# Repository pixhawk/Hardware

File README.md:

# Pixhawk Hardware Designs

<div align="center">

</div>

[Pixhawk](http://pixhawk.org) is an independent open-hardware project that aims to provide "the gold standard" for readily-available, hiqh-quality and low-cost autopilot hardware designs for the academic, hobby and developer communities.
Pixhawk supports multiple flight stacks: PX4 ® and ArduPilot ®.

> [!NOTE]
> Designs are provided for a number of components used in unmanned vehicles, including: Autopilots (Flight Management Units - FMUs), ESCs (electronic speed controllers), optical flow sensors, etc.

## What are Open Hardware Designs?

The [Pixhawk project](https://pixhawk.org/) provides open hardware designs following the [OSHW 1.1 definition](https://www.oshwa.org/definition/).

In essence, this definition allows anyone to freely study, modify, distribute, make, and sell the designs (or hardware based on the designs) under the terms of a particular [open source licence](#licensing).

## Hardware Designs

Hardware designs delivered by the project are listed below.

<span id="fmu_designs"></span>

### FMU (Autopilot) Designs

Pixhawk FMU open designs include all information required to create an autopilot hardware product that is *firmware compatible* with other hardware created from the same design.
Manufacturers are encouraged to take the designs and create products that are best suited to a particular market or use case (e.g. for very small vehicles, or those that operate at environmental extremes).

> [!NOTE]
> While a physical connector standard is not mandated, newer products generally follow the [Pixhawk Connector Standard](https://pixhawk.org/pixhawk-connector-standard/).

#### Design Specifications

Designs are *usually* specified in the form of *schematics* that show all included components (CPU, sensors, etc.), how they are connected, and their pin mappings.
They may also include a BOM (bill of materials).

> [!NOTE]
> Not all designs deliver schematics.
> A minimal design needs to contain enough information for manufacturers to create a compatible products; this can also be achieved using a precise pinout definition and information about connections of internal/external busses, etc.

#### Open Reference Hardware

The project provides *open reference hardware/layouts* for **some** open designs, in some versions.
These are provided in the form of PCB layout files.

The reference hardware files are shared under the same [license](#licenses) as the associated open design, and hence may be used in the same way(s).

#### FMU Versions

The Pixhawk project has evolved the FMU design through a number of verisons.

These are named using the designation: FMUvX (e.g.: FMUv1, FMUv2, FMUv3, FMUv4, etc.).
Higher FMU numbers indicate that the board is more recent, but may not indicate increased capability (versions can be almost identical - differing only in connector wiring).

The versions are listed below (with a high level overview of the main differences).

Version | Year | Lead Product | CPU | Other
--- | --- | --- | --- | ---
[FMUv1](FMUv1/README.md) & [IOv1](IOv1) | 2012 | None | 168 MHz M4 | (Discontinued) Original Flight Management Unit and Separate I/O board.
[FMUv2](FMUv2/README.md) | 2013 | Pixhawk 1 | 168 MHz M4 | Single board with STM32427VI processor.
[FMUv3](FMUv3_REV_D/README.md) | 2015 | Pixhawk 2 | 168 MHz M4 | Redundant sensors. Identical to FMUv2, but usable flash doubled to 2MB.
[FMUv4](FMUv4/README.md) | 2015 | Pixracer | 168 MHz M4 | Increased RAM. Faster CPU. More serial ports. No IO processor.
FMUv4X | 2017 | Pixhawk 3 Pro | 168 MHz M4 | Slightly increased RAM. More serial ports. IO processor. Redundant sensors.
[FMUv5](FMUv5/README.md) | 2018 | Pixhawk 4 | 200 MHz M7 | New processor (F7). Much faster. More RAM. More CAN busses. Much more configurable.<br>> **Note** Minimum specification provided (pinout info, but no schematics).
FMUv5X | 2019 | Pixhawk 5X | 200 MHz M7 | Temp-calibrated, redundant sensors.

> [!NOTE]
> Products based on Pixhawk designs are listed here: [PX4 User Guide > Pixhawk Series](https://docs.px4.io/main/en/flight_controller/pixhawk_series.html#pixhawk-series).

#### Derived FMU Products

Commercial products that are *derived* (under the terms of the open source license) from the Pixhawk FMU designs must provide their schematics and other information.

Relevant products are listed below:

- [MindPX V2 Hardware](MindPXv2/README.md)

### Sapog ESC

- [Sapog ESC](https://github.com/PX4/sapog) Hardware - The directory [sapog_reference_hardware](sapog_reference_hardware/README.md) contains the reference hardware design for the Sapog ESC firmware.

### Other

- [AIRSPEEDv1](AIRSPEEDv1) - 
- [FLOWv1](FLOWv1)
- [IMUv3_REV_C](IMUv3_REV_C)
- [PSMv3_REV_C](PSMv3_REV_C)

## Dev Call

Pixhawk standards are developed in a weekly public developer call.

The call is shown in the [Dronecode calendar](https://www.dronecode.org/calendar/) as: *Pixhawk Hardware Standards Weekly Call* (all call details are in the entry).

<span id="licensing"></span>
## Licensing and Trademarks

Pixhawk project schematics and reference designs are licensed under [CC BY-SA 3](https://creativecommons.org/licenses/by-sa/3.0/legalcode).

The license allows you to use, sell, share, modify and build on the files in almost any way you like - provided that you give credit/attribution, and that you share any changes that you make under the same open source license (see the [human readable version of the license](https://creativecommons.org/licenses/by-sa/3.0/) for a concise summary of the rights and obligations).

> [!NOTE]
> Boards that are *derived directly* from Pixhawk schematic files (or reference boards) must be open sourced.
> They can't be commercially licensed as proprietary products.

Manufacturers can create (compatible) *fully independent products* by first generating fresh schematic files that have the same pin mapping/components as the FMU designs.
Products that are based on independently created schematics are considered original works, and can be licensed as required.

## Trademarks

The term *Pixhawk* is a trademark, and may not be used in product names without explicit permission from the trademark owner.

Typically this trademark is granted to the first board based on a particular FMU design and/or boards that use Pixhawk open reference hardware layouts.

> [!NOTE]
> A "Pixhawk" is an autopilot that has been been given permission to use the Pixhawk trademark in its name.
> While other boards are based on the "Pixhawk FMU Standard", the are not *strictly speaking* "Pixhawks".

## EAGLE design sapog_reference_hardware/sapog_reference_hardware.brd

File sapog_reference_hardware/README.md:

# Reference Hardware for PX4 Sapog

This directory contains the reference hardware design for
[PX4 Sapog](https://kb.zubax.com/x/cYAh) - an advanced open source ESC firmware.

This specific design is intended as an application note;
the main knowledge to gather from this design is the pinout of the MCU and its immediate connections.
The design is implemented in Eagle, version 7 or newer is required.

## Resources

* **[HOMEPAGE](https://kb.zubax.com/x/cYAh)**
* **[SUPPORT & FEEDBACK](https://forum.zubax.com/)**
* **[FIRMWARE ON GITHUB](https://github.com/PX4/sapog)**

## Design guidelines

1. When choosing the power transistors, keep their dynamic characteristics in mind:
the switching time must be under 50 nanoseconds.
Sapog employs somewhat unorthodox methods of state estimation which require a high-speed inverter.
2. The RC filters in the phase voltage feedback circuits should be designed so that their cutoff frequency
is around 19 kHz and the output impedance does not exceed 8 kohm.
3. Unless your maximum supply voltage exceeds 25 V (6S), do not change the DC link voltage measurement divider.

## License

The design is distributed under the terms of the
Creative Commons Attribution-ShareAlike 3.0 Unported license (CC BY-SA 3.0).

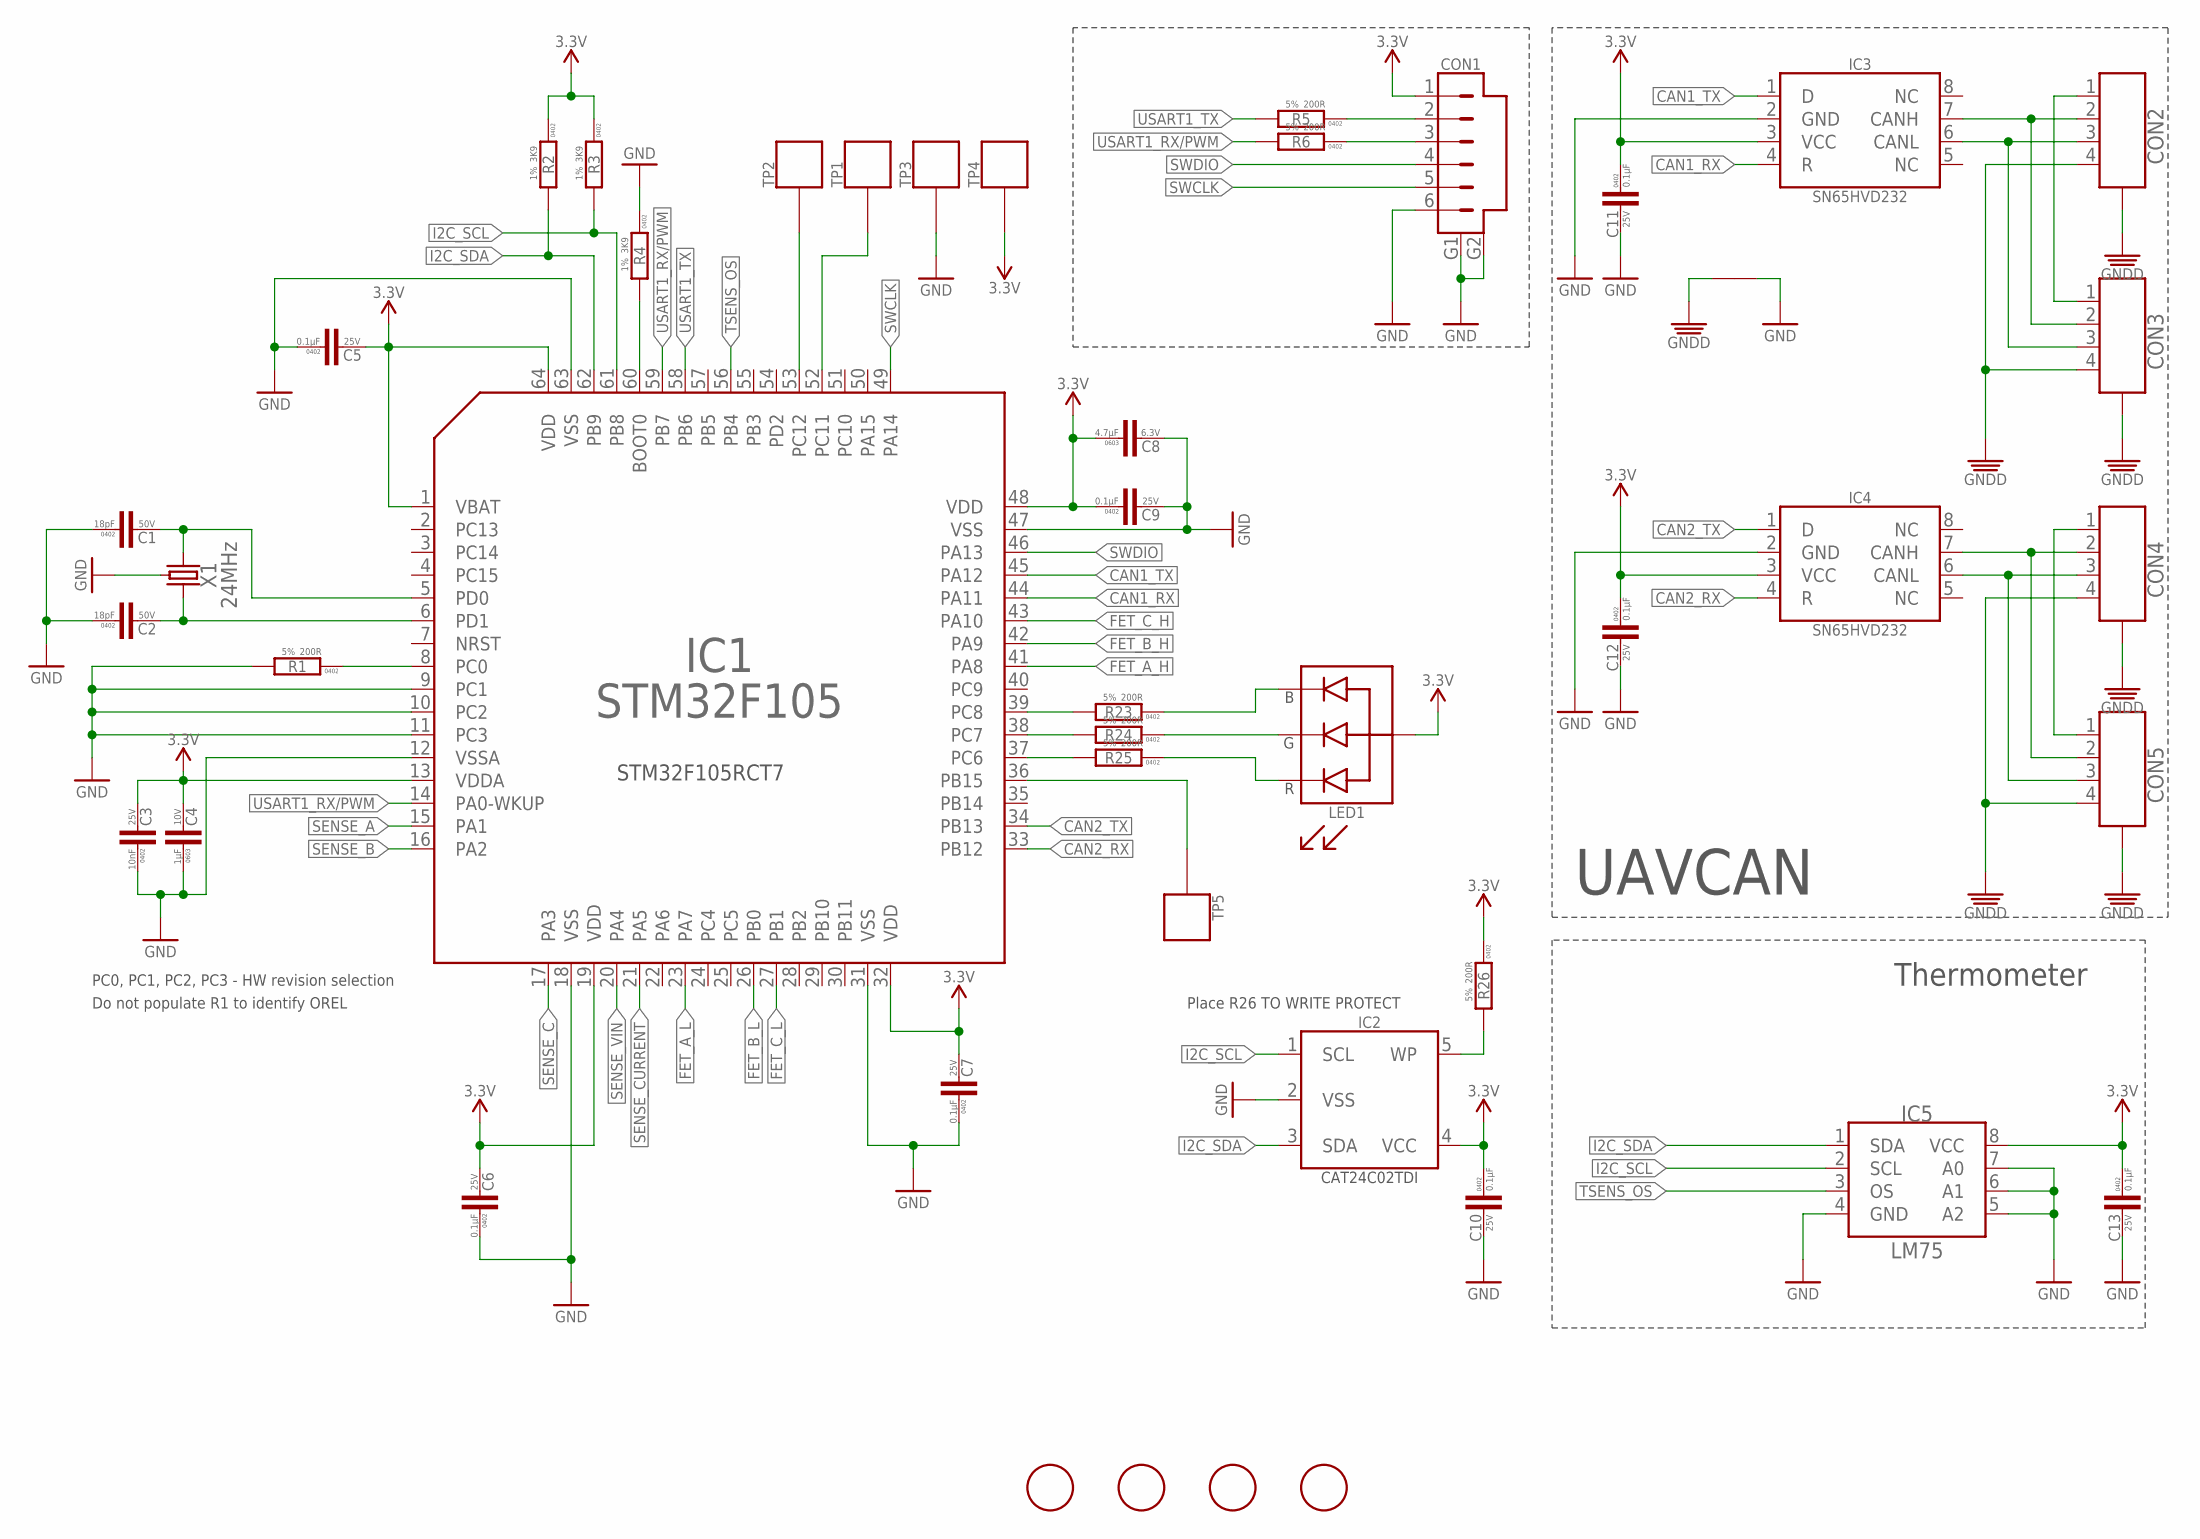
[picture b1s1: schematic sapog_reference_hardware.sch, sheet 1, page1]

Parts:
C1, C2: 18pF; C0402
C3: 10nF; C0402
C4: 1µF; C0603
C5, C6, C7, C9, C10, C11, C12, C13: 0.1µF; C0402
C8: 4.7µF; C0603
CON1: SM06B-SRSS-TB; SM06B; PARTNO SM06B-SRSS-TB
CON2, CON3, CON4, CON5: CON-4P-RA-JST_GH; JST_GH-4P-RA
FD1, FD2, FD3, FD4: FIDUCIALMOUNT; FIDUCIA-MOUNT
IC1: STM32F105; TQFP64-10X10; DIGIKEY# 497-11547-ND
IC2: CAT24C02; SOT23-5L
IC3, IC4: SN65HVD232D; SOIC8
IC5: LM75BD-TSSOP8; TSSOP8
LED1: LTST-C19HE1WT; LITE_ON_RGB_LED
R1: 200R; R0402
R2, R3, R4: 3K9; R0402
R5, R6, R23, R24, R25, R26: 200R; R0402; PARTNO RC0402FR-07240RL
TP1, TP2, TP3, TP4, TP5: PAD.05; PAD.05X.05; PARTNO *
U$2: CONNECTION
X1: 24MHz; OSCILLATOR-3.2X2.5; DIGIKEY# 1253-1198-1-ND

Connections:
BOOT0: IC1.60 (BOOT0), R4.2
CAN1_RX: IC1.44 (PA11), IC3.4 (R)
CAN1_TX: IC1.45 (PA12), IC3.1 (D)
CAN2_RX: IC1.33 (PB12), IC4.4 (R)
CAN2_TX: IC1.34 (PB13), IC4.1 (D)
FET_A_H: IC1.41 (PA8); also elsewhere on the board
FET_A_L: IC1.23 (PA7); also elsewhere on the board
FET_B_H: IC1.42 (PA9); also elsewhere on the board
FET_B_L: IC1.26 (PB0); also elsewhere on the board
FET_C_H: IC1.43 (PA10); also elsewhere on the board
FET_C_L: IC1.27 (PB1); also elsewhere on the board
GND: C1.1, C2.1, C3.1, C4.P$1 (1), C5.1, C6.1, C7.1, C8.P$2 (2), C9.2, C10.2, C11.2, C12.2, C13.2, CON1.6, CON1.G1, CON1.G2, IC1.9 (PC1), IC1.10 (PC2), IC1.11 (PC3), IC1.12 (VSSA), IC1.18 (VSS), IC1.31 (VSS), IC1.47 (VSS), IC1.63 (VSS), IC2.2 (VSS), IC3.2 (GND), IC4.2 (GND), IC5.4 (GND), IC5.5 (A2), IC5.6 (A1), IC5.7 (A0), R1.2, R4.1, TP3.P$1, U$2.P$2, X1.2 (GND), X1.4 (GND); also elsewhere on the board
GNDD: CON2.4, CON2.M$0 (GND), CON2.M$1 (GND), CON3.4, CON3.M$0 (GND), CON3.M$1 (GND), CON4.4, CON4.M$0 (GND), CON4.M$1 (GND), CON5.4, CON5.M$0 (GND), CON5.M$1 (GND), U$2.P$1
I2C_SCL: IC1.61 (PB8), IC2.1 (SCL), IC5.2 (SCL), R3.2
I2C_SDA: IC1.62 (PB9), IC2.3 (SDA), IC5.1 (SDA), R2.2
unnamed: CON1.2, R5.1
unnamed: CON1.3, R6.1
unnamed: IC1.37 (PC6), R25.2
unnamed: LED1.B, R23.1
unnamed: LED1.R, R25.1
unnamed: IC1.8 (PC0), R1.1
unnamed: IC2.5 (WP), R26.2
unnamed: IC1.38 (PC7), R24.2
unnamed: C1.2, IC1.5 (PD0), X1.3 (2)
unnamed: IC1.39 (PC8), R23.2
unnamed: CON4.1, CON5.1
unnamed: CON4.2, CON5.2, IC4.7 (CANH)
unnamed: C2.2, IC1.6 (PD1), X1.1
unnamed: CON2.1, CON3.1
unnamed: CON2.2, CON3.2, IC3.7 (CANH)
unnamed: CON4.3, CON5.3, IC4.6 (CANL)
unnamed: CON2.3, CON3.3, IC3.6 (CANL)
unnamed: LED1.G, R24.1
unnamed: IC1.53 (PC12), TP2.P$1
unnamed: IC1.36 (PB15), TP5.P$1
unnamed: IC1.52 (PC11), TP1.P$1
SENSE_A: IC1.15 (PA1); also elsewhere on the board
SENSE_B: IC1.16 (PA2); also elsewhere on the board
SENSE_C: IC1.17 (PA3); also elsewhere on the board
SENSE_CURRENT: IC1.21 (PA5); also elsewhere on the board
SENSE_VIN: IC1.20 (PA4); also elsewhere on the board
SWCLK: CON1.5, IC1.49 (PA14)
SWDIO: CON1.4, IC1.46 (PA13)
TSENS_OS: IC1.56 (PB4), IC5.3 (OS)
USART1_RX/PWM: IC1.14 (PA0-WKUP), IC1.59 (PB7), R6.2
USART1_TX: IC1.58 (PB6), R5.2
VDD_3V3: C3.2, C4.P$2 (2), C5.2, C6.2, C7.2, C8.P$1 (1), C9.1, C10.1, C11.1, C12.1, C13.1, CON1.1, IC1.1 (VBAT), IC1.13 (VDDA), IC1.19 (VDD), IC1.32 (VDD), IC1.48 (VDD), IC1.64 (VDD), IC2.4 (VCC), IC3.3 (VCC), IC4.3 (VCC), IC5.8 (VCC), LED1.+ (A), R2.1, R3.1, R26.1, TP4.P$1; also elsewhere on the board

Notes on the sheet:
UAVCAN
PC0, PC1, PC2, PC3 - HW revision selection
Do not populate R1 to identify OREL
Thermometer
Place R26 TO WRITE PROTECT
STM32F105RCT7

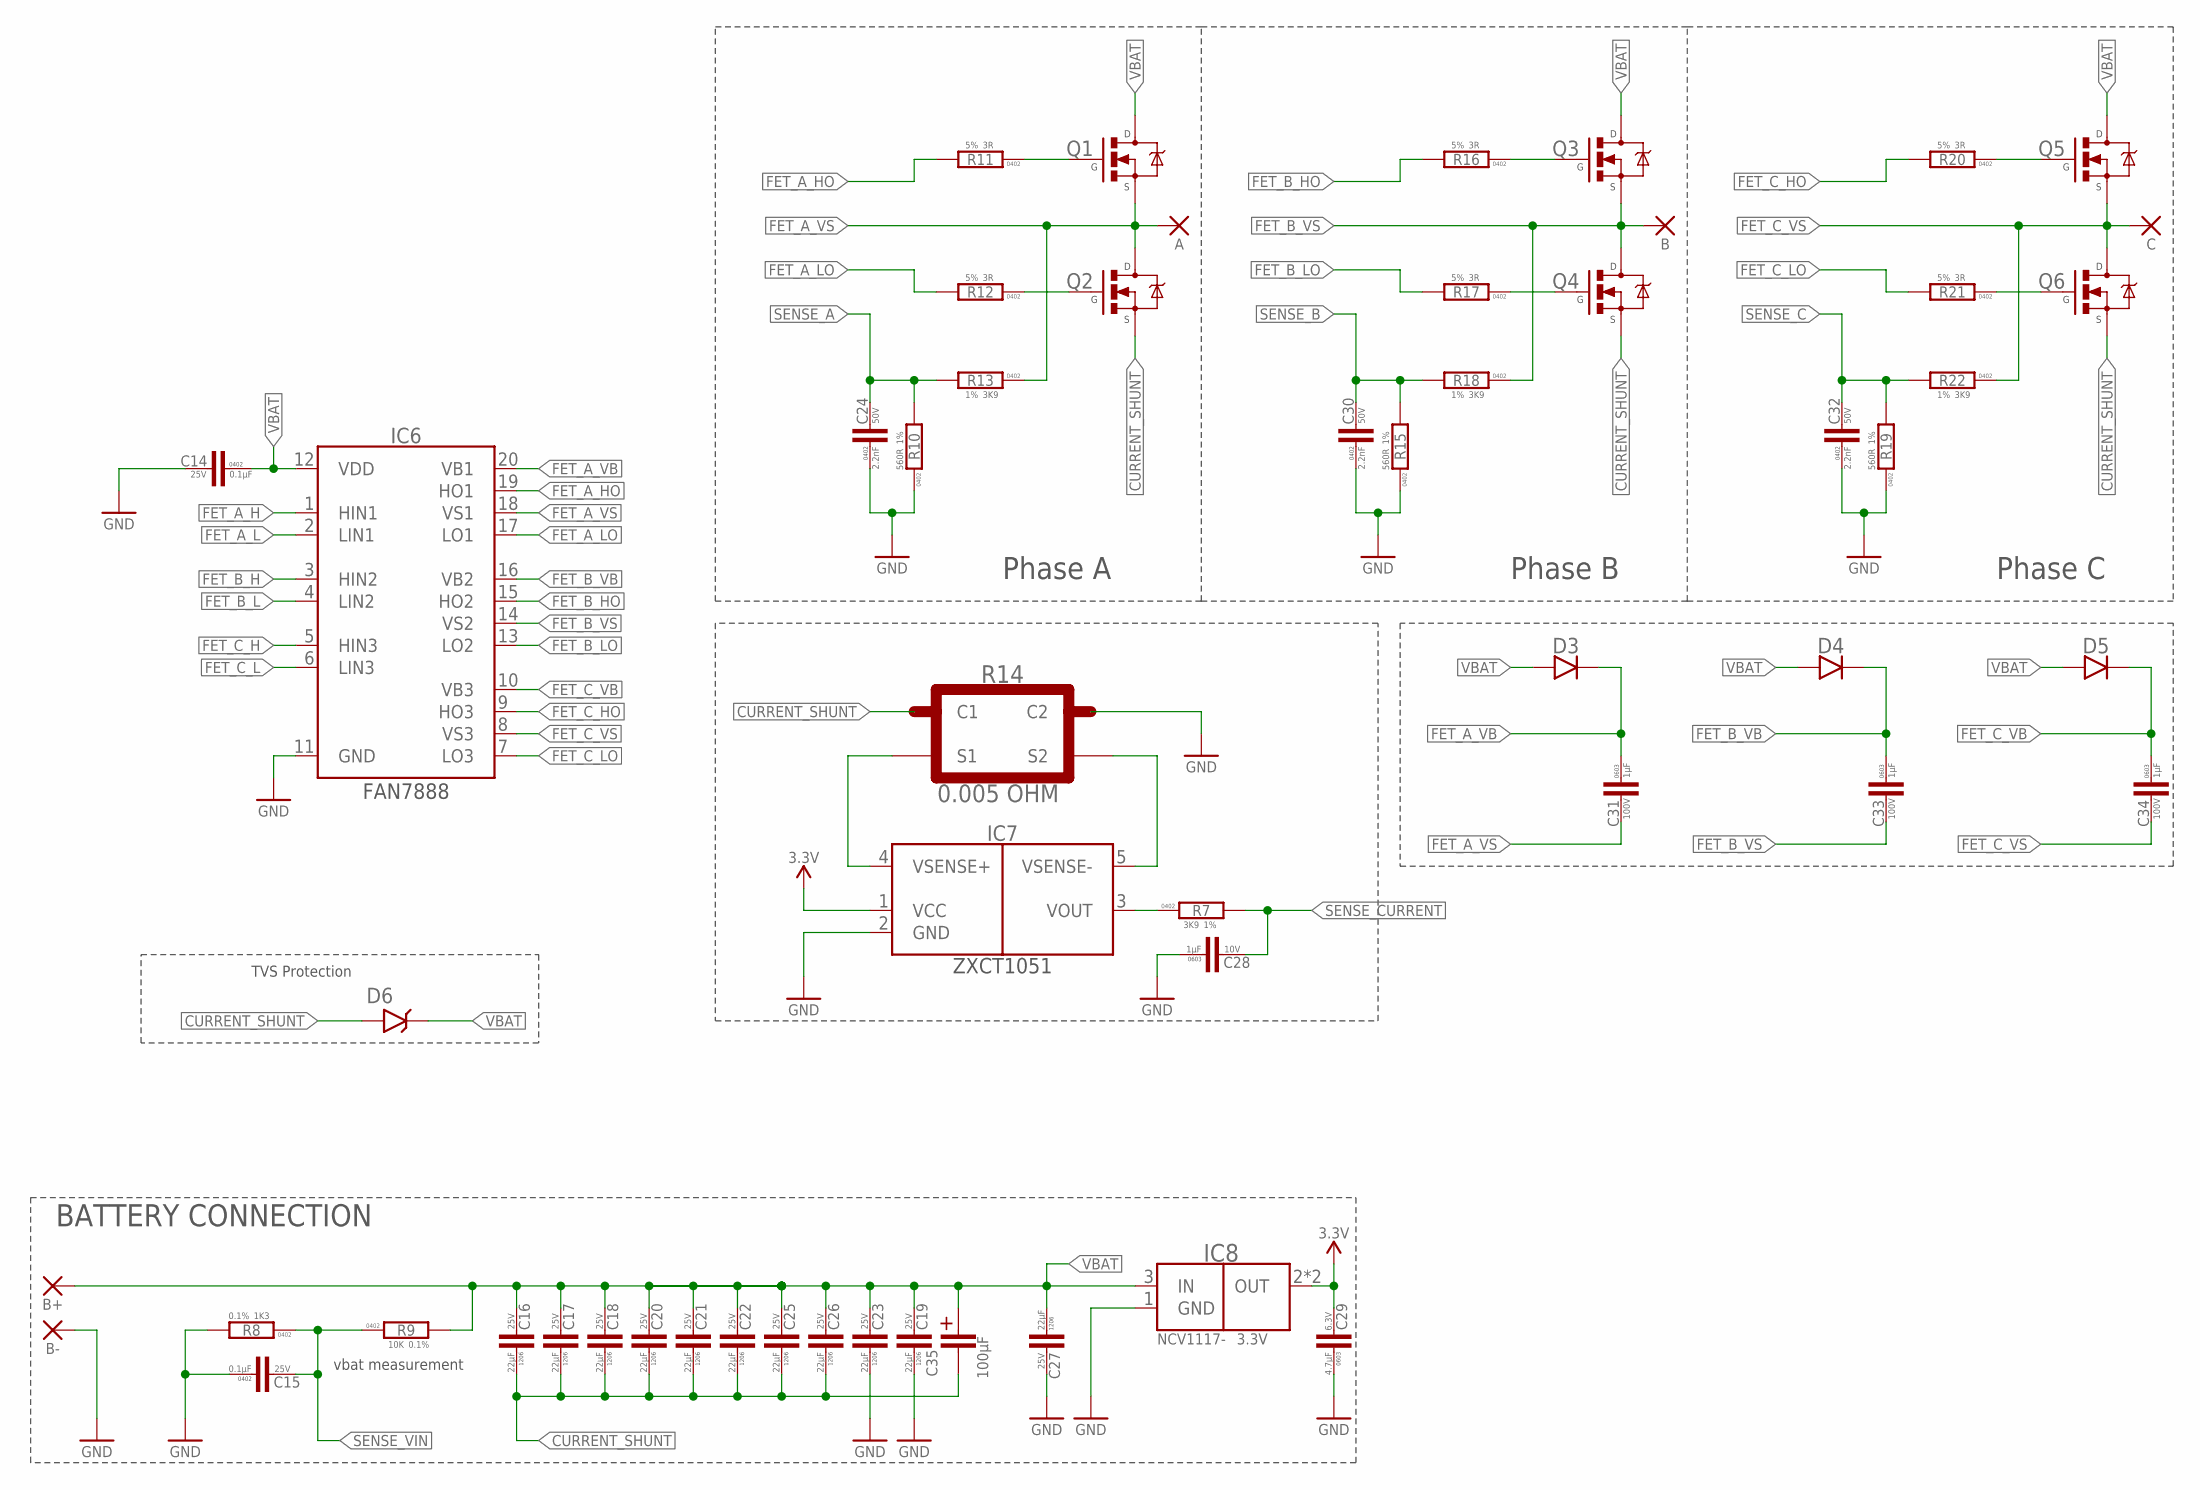
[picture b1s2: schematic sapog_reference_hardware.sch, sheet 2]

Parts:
A: WIREPADSMD5-2,5; 5-2,5
B: WIREPADSMD5-2,5; 5-2,5
B+: WIREPADSMD5-2,5; 5-2,5
B-: WIREPADSMD5-2,5; 5-2,5
C: WIREPADSMD5-2,5; 5-2,5
C14, C15: 0.1µF; C0402
C16, C17, C18, C19, C20, C21, C22, C23, C25, C26, C27: 22µF; C1206
C24, C30, C32: 2.2nF; C0402
C28, C31, C33, C34: 1µF; C0603
C29: 4.7µF; C0603
C35: 100µF; 3024
D3, D4, D5: BAS21AHT1G; SOD323
D6: 1KSMB20A; SMB
IC6: FAN7888; SOIC20; PARTNO FAN7888MX
IC7: ZXCT1051; SOT23-5L
IC8: 3.3V; SOT-223
Q1, Q2, Q3, Q4, Q5, Q6: BSC019N04NS-DFN5X6; DFN5X6
R7, R13, R18, R22: 3K9; R0402
R8: 1K3; R0402
R9: 10K; R0402
R10, R15, R19: 560R; R0402
R11, R12, R16, R17, R20, R21: 3R; R0402
R14: 0.005 OHM; 2010_CURRENT_SHUNT

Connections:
BLABLA: IC7.3 (VOUT), R7.1
CURRENT_SHUNT: C16.P$1 (1), C17.P$1 (1), C18.P$1 (1), C20.P$1 (1), C21.P$1 (1), C22.P$1 (1), C25.P$1 (1), C26.P$1 (1), C35.-, D6.A, Q2.1S (S), Q2.2S (S), Q2.3S (S), Q4.1S (S), Q4.2S (S), Q4.3S (S), Q6.1S (S), Q6.2S (S), Q6.3S (S), R14.CURRENT1 (C1)
FET_A_H: IC6.1 (HIN1); also elsewhere on the board
FET_A_HO: IC6.19 (HO1), R11.2
FET_A_L: IC6.2 (LIN1); also elsewhere on the board
FET_A_LO: IC6.17 (LO1), R12.2
FET_A_VB: C31.P$1 (1), D3.C, IC6.20 (VB1)
FET_A_VS: A.1, C31.P$2 (2), IC6.18 (VS1), Q1.1S (S), Q1.2S (S), Q1.3S (S), Q2.5D (D), Q2.6D (D), Q2.7D (D), Q2.8D (D), R13.1
FET_B_H: IC6.3 (HIN2); also elsewhere on the board
FET_B_HO: IC6.15 (HO2), R16.2
FET_B_L: IC6.4 (LIN2); also elsewhere on the board
FET_B_LO: IC6.13 (LO2), R17.2
FET_B_VB: C33.P$1 (1), D4.C, IC6.16 (VB2)
FET_B_VS: B.1, C33.P$2 (2), IC6.14 (VS2), Q3.1S (S), Q3.2S (S), Q3.3S (S), Q4.5D (D), Q4.6D (D), Q4.7D (D), Q4.8D (D), R18.1
FET_C_H: IC6.5 (HIN3); also elsewhere on the board
FET_C_HO: IC6.9 (HO3), R20.2
FET_C_L: IC6.6 (LIN3); also elsewhere on the board
FET_C_LO: IC6.7 (LO3), R21.2
FET_C_VB: C34.P$1 (1), D5.C, IC6.10 (VB3)
FET_C_VS: C.1, C34.P$2 (2), IC6.8 (VS3), Q5.1S (S), Q5.2S (S), Q5.3S (S), Q6.5D (D), Q6.6D (D), Q6.7D (D), Q6.8D (D), R22.1
GND: B-.1, C14.2, C15.1, C19.P$1 (1), C23.P$1 (1), C24.1, C27.P$2 (2), C28.P$1 (1), C29.P$1 (1), C30.1, C32.1, IC6.11 (GND), IC7.2 (GND), IC8.1 (GND), R8.2, R10.1, R14.CURRENT2 (C2), R15.1, R19.1; also elsewhere on the board
unnamed: Q2.4G (G), R12.1
unnamed: Q3.4G (G), R16.1
unnamed: Q4.4G (G), R17.1
unnamed: Q5.4G (G), R20.1
unnamed: IC7.5 (VSENSE-), R14.SENSE2 (S2)
unnamed: Q1.4G (G), R11.1
unnamed: IC7.4 (VSENSE+), R14.SENSE1 (S1)
unnamed: Q6.4G (G), R21.1
SENSE_A: C24.2, R10.2, R13.2; also elsewhere on the board
SENSE_B: C30.2, R15.2, R18.2; also elsewhere on the board
SENSE_C: C32.2, R19.2, R22.2; also elsewhere on the board
SENSE_CURRENT: C28.P$2 (2), R7.2; also elsewhere on the board
SENSE_VIN: C15.2, R8.1, R9.1; also elsewhere on the board
VBAT: B+.1, C14.1, C16.P$2 (2), C17.P$2 (2), C18.P$2 (2), C19.P$2 (2), C20.P$2 (2), C21.P$2 (2), C22.P$2 (2), C23.P$2 (2), C25.P$2 (2), C26.P$2 (2), C27.P$1 (1), C35.+, D3.A, D4.A, D5.A, D6.C, IC6.12 (VDD), IC8.3 (IN), Q1.5D (D), Q1.6D (D), Q1.7D (D), Q1.8D (D), Q3.5D (D), Q3.6D (D), Q3.7D (D), Q3.8D (D), Q5.5D (D), Q5.6D (D), Q5.7D (D), Q5.8D (D), R9.2
VDD_3V3: C29.P$2 (2), IC7.1 (VCC), IC8.2 (OUT), IC8.4 (OUT); also elsewhere on the board

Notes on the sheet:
vbat measurement
BATTERY CONNECTION
Phase A
Phase B
Phase C
TVS Protection

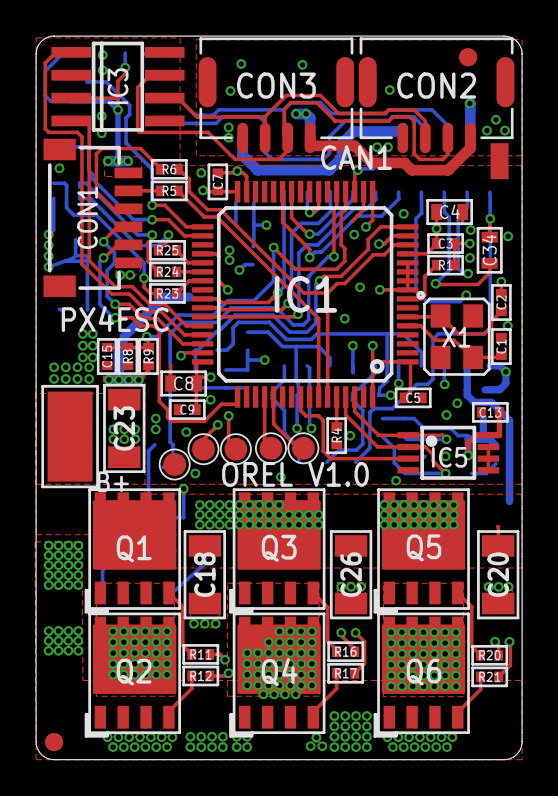
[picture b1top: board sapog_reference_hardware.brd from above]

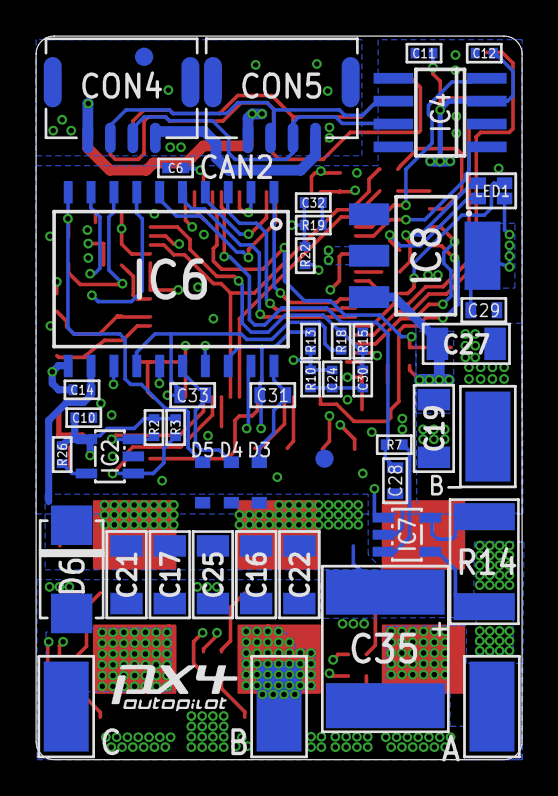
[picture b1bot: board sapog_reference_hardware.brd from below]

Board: 4 copper layers, 27.0 x 40.2 mm, 103 parts (50 on the bottom side), 70 nets.

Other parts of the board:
U$1: REF_BOARD_OUTLINE
U$3: PX4-LOGO-7MM

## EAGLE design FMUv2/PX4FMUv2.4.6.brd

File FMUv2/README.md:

# FMUv2 Pixhawk Open Hardware Design

FMUv1 & FMUv2 boards
 Pixhawk v1 Hardware

Design files are EAGLE CAD files (can be viewed with the free version)
www.cadsoftusa.com/

And BOM management is performed using Bob Starr's BOM-EX plugin:
http://www.bobstarr.net/pages/downloads.html

## Licensing & Trademarks

Information on licensing and trademarks for Pixhawk designs can be found here: [Pixhawk Licensing](../README.md#license)

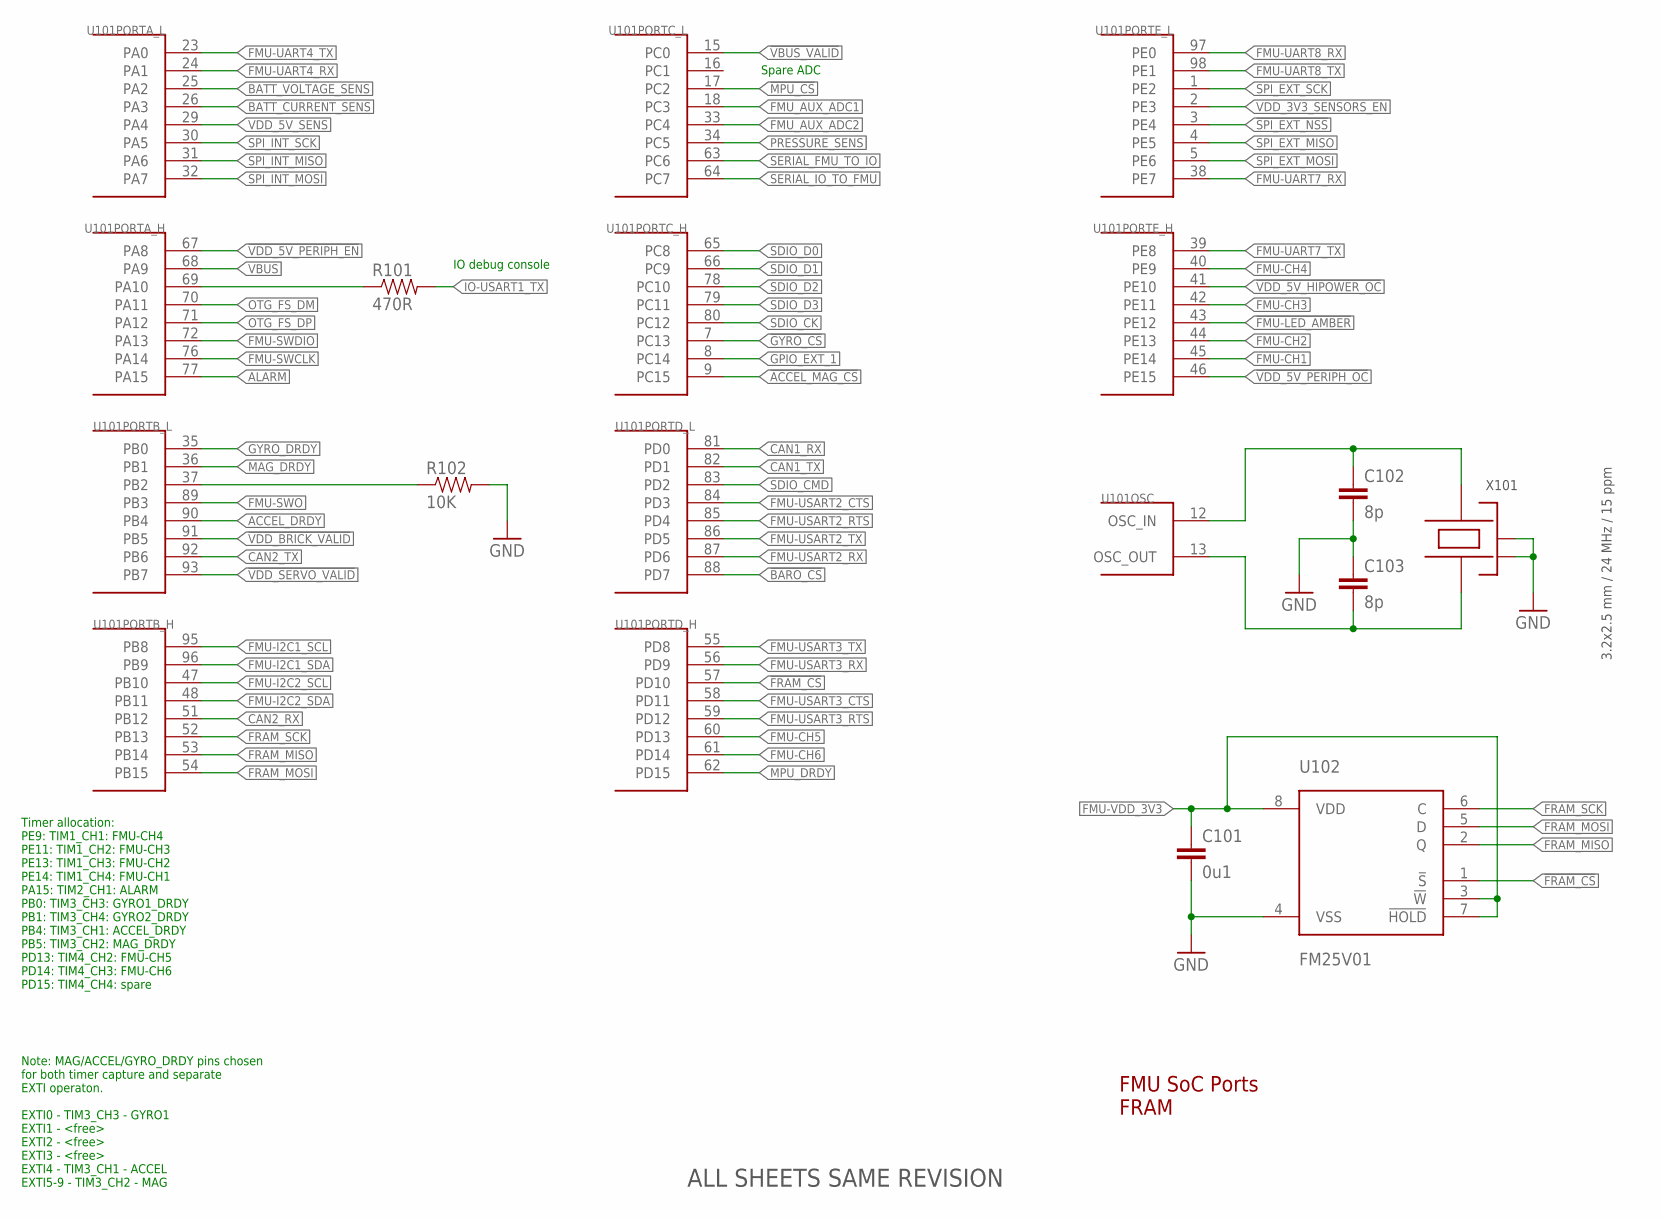
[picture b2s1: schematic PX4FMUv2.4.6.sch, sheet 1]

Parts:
C101: 0u1; 0402-CAP; PARTNO CC0402ZRY5V7BB104
C102, C103: 8p; 0402-CAP; PARTNO C1005C0G1H080C
R101: 470R; 0402-RES; PARTNO RC0402FR-07470RL
R102: 10K; 0402-RES; PARTNO RC0402FR-0710KL
U101: STM32F4X7VX; TQFP100; PARTNO STM32F427VI
U102: FM25V01; SO08; PARTNO FM25V01-G
X101: 3.2x2.5 mm / 24 MHz / 15 ppm; OSCILLATOR-3.2X2.5; PARTNO NX3225SA-24.000000MHZ

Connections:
!ACCEL_MAG_CS: U101.9 (PC15); also elsewhere on the board
!BARO_CS: U101.88 (PD7); also elsewhere on the board
!FMU-LED_AMBER: U101.43 (PE12); also elsewhere on the board
!FRAM_CS: U101.57 (PD10), U102.1 (!S)
!GYRO_CS: U101.7 (PC13); also elsewhere on the board
!MPU_CS: U101.17 (PC2); also elsewhere on the board
!SPI_EXT_NSS: U101.3 (PE4); also elsewhere on the board
!VBUS_VALID: U101.15 (PC0); also elsewhere on the board
!VDD_5V_HIPOWER_OC: U101.41 (PE10); also elsewhere on the board
!VDD_5V_PERIPH_EN: U101.67 (PA8); also elsewhere on the board
!VDD_5V_PERIPH_OC: U101.46 (PE15); also elsewhere on the board
!VDD_BRICK_VALID: U101.91 (PB5); also elsewhere on the board
!VDD_SERVO_VALID: U101.93 (PB7); also elsewhere on the board
ACCEL_DRDY: U101.90 (PB4); also elsewhere on the board
ALARM: U101.77 (PA15); also elsewhere on the board
BATT_CURRENT_SENS: U101.26 (PA3); also elsewhere on the board
BATT_VOLTAGE_SENS: U101.25 (PA2); also elsewhere on the board
CAN1_RX: U101.81 (PD0); also elsewhere on the board
CAN1_TX: U101.82 (PD1); also elsewhere on the board
CAN2_RX: U101.51 (PB12); also elsewhere on the board
CAN2_TX: U101.92 (PB6); also elsewhere on the board
FMU-CH1: U101.45 (PE14); also elsewhere on the board
FMU-CH2: U101.44 (PE13); also elsewhere on the board
FMU-CH3: U101.42 (PE11); also elsewhere on the board
FMU-CH4: U101.40 (PE9); also elsewhere on the board
FMU-CH5: U101.60 (PD13); also elsewhere on the board
FMU-CH6: U101.61 (PD14); also elsewhere on the board
FMU-I2C1_SCL: U101.95 (PB8); also elsewhere on the board
FMU-I2C1_SDA: U101.96 (PB9); also elsewhere on the board
FMU-I2C2_SCL: U101.47 (PB10); also elsewhere on the board
FMU-I2C2_SDA: U101.48 (PB11); also elsewhere on the board
FMU-SWCLK: U101.76 (PA14); also elsewhere on the board
FMU-SWDIO: U101.72 (PA13); also elsewhere on the board
FMU-SWO: U101.89 (PB3); also elsewhere on the board
FMU-UART4_RX: U101.24 (PA1); also elsewhere on the board
FMU-UART4_TX: U101.23 (PA0); also elsewhere on the board
FMU-UART7_RX: U101.38 (PE7); also elsewhere on the board
FMU-UART7_TX: U101.39 (PE8); also elsewhere on the board
FMU-UART8_RX: U101.97 (PE0); also elsewhere on the board
FMU-UART8_TX: U101.98 (PE1); also elsewhere on the board
FMU-USART2_CTS: U101.84 (PD3); also elsewhere on the board
FMU-USART2_RTS: U101.85 (PD4); also elsewhere on the board
FMU-USART2_RX: U101.87 (PD6); also elsewhere on the board
FMU-USART2_TX: U101.86 (PD5); also elsewhere on the board
FMU-USART3_CTS: U101.58 (PD11); also elsewhere on the board
FMU-USART3_RTS: U101.59 (PD12); also elsewhere on the board
FMU-USART3_RX: U101.56 (PD9); also elsewhere on the board
FMU-USART3_TX: U101.55 (PD8); also elsewhere on the board
FMU-VDD_3V3: C101.P$1 (1), U102.3 (!W), U102.7 (!HOLD), U102.8 (VDD); also elsewhere on the board
FMU_AUX_ADC1: U101.18 (PC3); also elsewhere on the board
FMU_AUX_ADC2: U101.33 (PC4); also elsewhere on the board
FRAM_MISO: U101.53 (PB14), U102.2 (Q)
FRAM_MOSI: U101.54 (PB15), U102.5 (D)
FRAM_SCK: U101.52 (PB13), U102.6 (C)
GND: C101.P$2 (2), C102.P$2 (2), C103.P$1 (1), R102.P$2 (2), U102.4 (VSS), X101.2 (NC_2), X101.4 (NC_4); also elsewhere on the board
GPIO_EXT_1: U101.8 (PC14); also elsewhere on the board
GYRO_DRDY: U101.35 (PB0); also elsewhere on the board
IO-USART1_TX: R101.P$2 (2); also elsewhere on the board
MAG_DRDY: U101.36 (PB1); also elsewhere on the board
MPU_DRDY: U101.62 (PD15); also elsewhere on the board
unnamed: C103.P$2 (2), U101.13 (OSC_OUT), X101.1
unnamed: C102.P$1 (1), U101.12 (OSC_IN), X101.3
unnamed: R101.P$1 (1), U101.69 (PA10)
OTG_FS_DM: U101.70 (PA11); also elsewhere on the board
OTG_FS_DP: U101.71 (PA12); also elsewhere on the board
PB2-BOOT1: R102.P$1 (1), U101.37 (PB2)
PRESSURE_SENS: U101.34 (PC5); also elsewhere on the board
SDIO_CK: U101.80 (PC12); also elsewhere on the board
SDIO_CMD: U101.83 (PD2); also elsewhere on the board
SDIO_D0: U101.65 (PC8); also elsewhere on the board
SDIO_D1: U101.66 (PC9); also elsewhere on the board
SDIO_D2: U101.78 (PC10); also elsewhere on the board
SDIO_D3: U101.79 (PC11); also elsewhere on the board
SERIAL_FMU_TO_IO: U101.63 (PC6); also elsewhere on the board
SERIAL_IO_TO_FMU: U101.64 (PC7); also elsewhere on the board
SPI_EXT_MISO: U101.4 (PE5); also elsewhere on the board
SPI_EXT_MOSI: U101.5 (PE6); also elsewhere on the board
SPI_EXT_SCK: U101.1 (PE2); also elsewhere on the board
SPI_INT_MISO: U101.31 (PA6); also elsewhere on the board
SPI_INT_MOSI: U101.32 (PA7); also elsewhere on the board
SPI_INT_SCK: U101.30 (PA5); also elsewhere on the board
VBUS: U101.68 (PA9); also elsewhere on the board
VDD_3V3_SENSORS_EN: U101.2 (PE3); also elsewhere on the board
VDD_5V_SENS: U101.29 (PA4); also elsewhere on the board

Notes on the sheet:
FMU SoC Ports FRAM
Note: MAG/ACCEL/GYRO_DRDY pins chosen for both timer capture and separate EXTI operaton. EXTI0 - TIM3_CH3 - GYRO1 EXTI1 - <free> EXTI2 - <free> EXTI3 - <free> EXTI4 - TIM3_CH1 - ACCEL EXTI5-9 - TIM3_CH2 - MAG
Timer allocation: PE9: TIM1_CH1: FMU-CH4 PE11: TIM1_CH2: FMU-CH3 PE13: TIM1_CH3: FMU-CH2 PE14: TIM1_CH4: FMU-CH1 PA15: TIM2_CH1: ALARM PB0: TIM3_CH3: GYRO1_DRDY PB1: TIM3_CH4: GYRO2_DRDY PB4: TIM3_CH1: ACCEL_DRDY PB5: TIM3_CH2: MAG_DRDY PD13: TIM4_CH2: FMU-CH5 PD14: TIM4_CH3: FMU-CH6 PD15: TIM4_CH4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
IO debug console
Spare ADC
ALL SHEETS SAME REVISION

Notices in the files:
FMUv2/PX4FMUv2.4.6.brd:
(c) 2013 mjs/lm/jo
PX4FMUv1.7.1.brd:
(c) 2012 mjs / lm
